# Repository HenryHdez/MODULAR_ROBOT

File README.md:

# **MODULAR ROBOT **
# **PROJECT "PCB"**
Here are all the PCB's for manufacturing the EMERGE modular robot.
# **PROJECT "Optimization_Algorithms.rar" CONTENT**
The content of this project is divided into three sections:
* The first "Module" project must be programmed in all modules of the robotic platform.
* The Second Project "Xbee_Snifer_Teraterm" must be programmed in the accessory card that has an Xbee module only (previously configured) and to perform the data registration you can use the project "Capture_Interface.rar" which is designed in MATLAB and simply begins its registration by pressing the Start button and turn on the robot.
To configure the Xbee module you can follow the following link;
http://xbee.cl/xbee-serie-2-configuracion/
* Finally, there are optimization algorithms, of which you must choose one and program it in the accessory that has the ultrasound sensor only.
# **PROJECT "Robot_Test.rar" CONTENT**
This project is used to test the different peripherals of the robot.
## Test_LED	
This code activates (Frecuency=10Hz) LED lights on each side.
## Test_All_Sensor	
The initialization routine is in charge of turning on the LED located next to each sensor, it will do it 5 times if there is communication with it, otherwise it will only do it once.
Once initialize each sensor, if one of them is obstructed turn on the LED that is next to it.
## Test_Motor	
This program turns on the motor led once it communicates with it, moves it from right to left and vice versa at intervals of 5 seconds.
## Test_Sensor_F1	
All LEDs turn on and off, if there is communication with the face sensor 1.
## Test_Sensor_F2	
All LEDs turn on and off, if there is communication with the face sensor 2.
## Test_Sensor_F3	
All LEDs turn on and off, if there is communication with the face sensor 3.
## Test_Sensor_F4	
All LEDs turn on and off, if there is communication with the face sensor 4.
## Test_CAN_Module_1
Each module sends and receives a data, if the data is accepted, turn on the led of face 2 in each module, otherwise it will not turn on.
## Test_CAN_Module_2	
CAN_Psoc_kit	
Show the information on the CAN bus on an LCD display.

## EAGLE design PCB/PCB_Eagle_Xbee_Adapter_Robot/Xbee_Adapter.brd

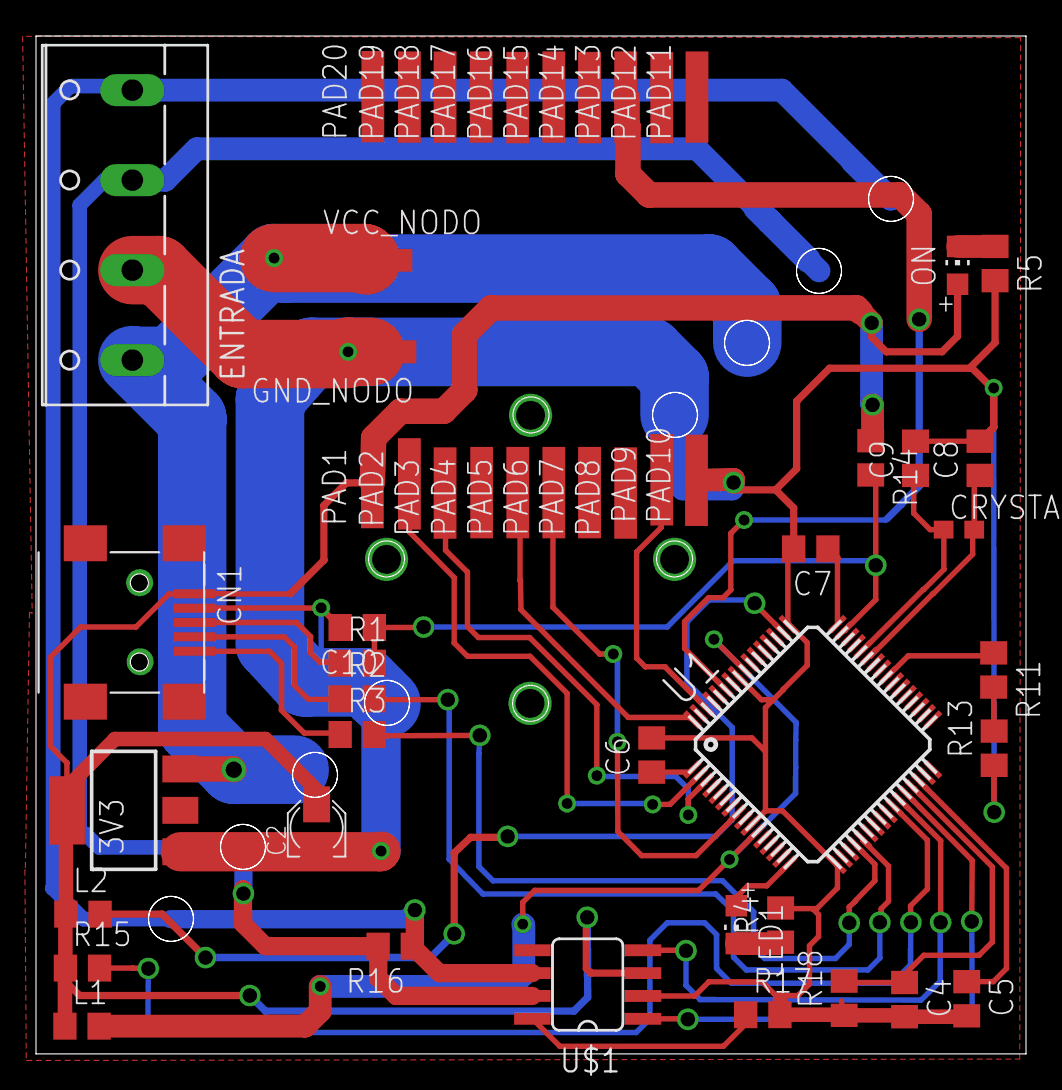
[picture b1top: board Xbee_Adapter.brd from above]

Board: 2 copper layers, 55.0 x 56.5 mm, 60 parts (0 on the bottom side), 34 nets.

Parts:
3V3: LD117AS33TR; SOT223
C2: PANASONIC_A
C4: 2200pF; C0805
C5: 10nF; C0805
C6, C7: 1u; C0805
C8: 36pF; C0805
C9: 18pF; C0805
C10: 0.1u; C0805
CANH_1_C1, CANH_1_C2: TPB2,54; B2,54
CANL_1_C1, CANL_1_C2: TPB2,54; B2,54
CN1: USB-MINIB
CRYSTAL: 32.768kHz; C0603
ENTRADA: W237-4
GND_1_C1, GND_1_C2: TPB2,54; B2,54
GND_NODO: SMD2,54-5,08
L1, L2: 330-600Ohm@1Mhz; R0805
LED1: CHIP-LED0805
ON: CHIP-LED0805
PAD1, PAD2, PAD3, PAD4, PAD5, PAD6, PAD7, PAD8, PAD9, PAD10, PAD11, PAD12, PAD13, PAD14, PAD15, PAD16, PAD17, PAD18, PAD19, PAD20: SMD2,54-5,08
R1, R2, R3, R11, R13, R15, R18: 0; R0805
R4: R0805
R5: 1K; R0805
R14: 4.7k; R0805
R16: 120; R0805
R17: 10k; R0805
U1: CY8C4247AZI-M485; TQFP64-10X10
U$1: SN65HVD230/1; SO8
VCC_2_C1, VCC_2_C2: TPB2,54; B2,54
VCC_NODO: SMD2,54-5,08

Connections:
3V3: 3V3.4, C2.+, CN1.VBUS, L1.1, L2.1, ON.A, PAD1.1, R14.1, R15.1, U$1.3
CANH: CANH_1_C1.TP, CANH_1_C2.TP, ENTRADA.3, R16.2, U$1.7
CANL: CANL_1_C1.TP, CANL_1_C2.TP, ENTRADA.4, R16.1, U$1.6
CAN_RX: U1.27, U$1.4
CAN_TX: U1.28, U$1.1
CMOD: C4.1, R18.2, U1.29
CTANK: C5.1, U1.30
GND: 3V3.1, C2.-, C4.2, C5.2, C6.2, C7.2, C8.2, C9.2, C10.2, CN1.D-, ENTRADA.2, GND_1_C1.TP, GND_1_C2.TP, GND_NODO.1, PAD10.1, R4.2, R5.2, R13.1, R17.2, R18.1, U1.10, U1.17, U1.49, U1.57, U$1.2
unnamed: CN1.D+, R1.1
unnamed: CN1.ID, R2.1
unnamed: CN1.GND, R3.1
unnamed: R11.2, R13.2
unnamed: LED1.A, U1.16
unnamed: LED1.C, R4.1
unnamed: R17.1, U$1.8
unnamed: ON.C, R5.1
P0_1: R11.1, U1.40
P0_4: C8.1, CRYSTAL.2, U1.43
P0_5: C9.1, CRYSTAL.1, U1.44
RESET_XBEE: PAD5.1, U1.64
RX_STRENGTH: PAD6.1, U1.8
SAR_BY: C6.1, U1.1
SLEEP_CTRL: PAD9.1, U1.62
SLEEP_XBEE: PAD13.1, U1.59
SWDCLK: R2.2, U1.21
SWDIO: R3.2, U1.20
UART_RX: PAD3.1, U1.3
UART_TX: PAD2.1, U1.2
VCCD: C7.1, U1.48
VCC_9-12V: 3V3.3, ENTRADA.1, VCC_2_C1.TP, VCC_2_C2.TP, VCC_NODO.1
VDDA: L1.2, U1.11, U1.56
VDDD: L2.2, U1.50
VDDIO: R15.2, U1.26
XRES: C10.1, R1.2, R14.2, U1.47

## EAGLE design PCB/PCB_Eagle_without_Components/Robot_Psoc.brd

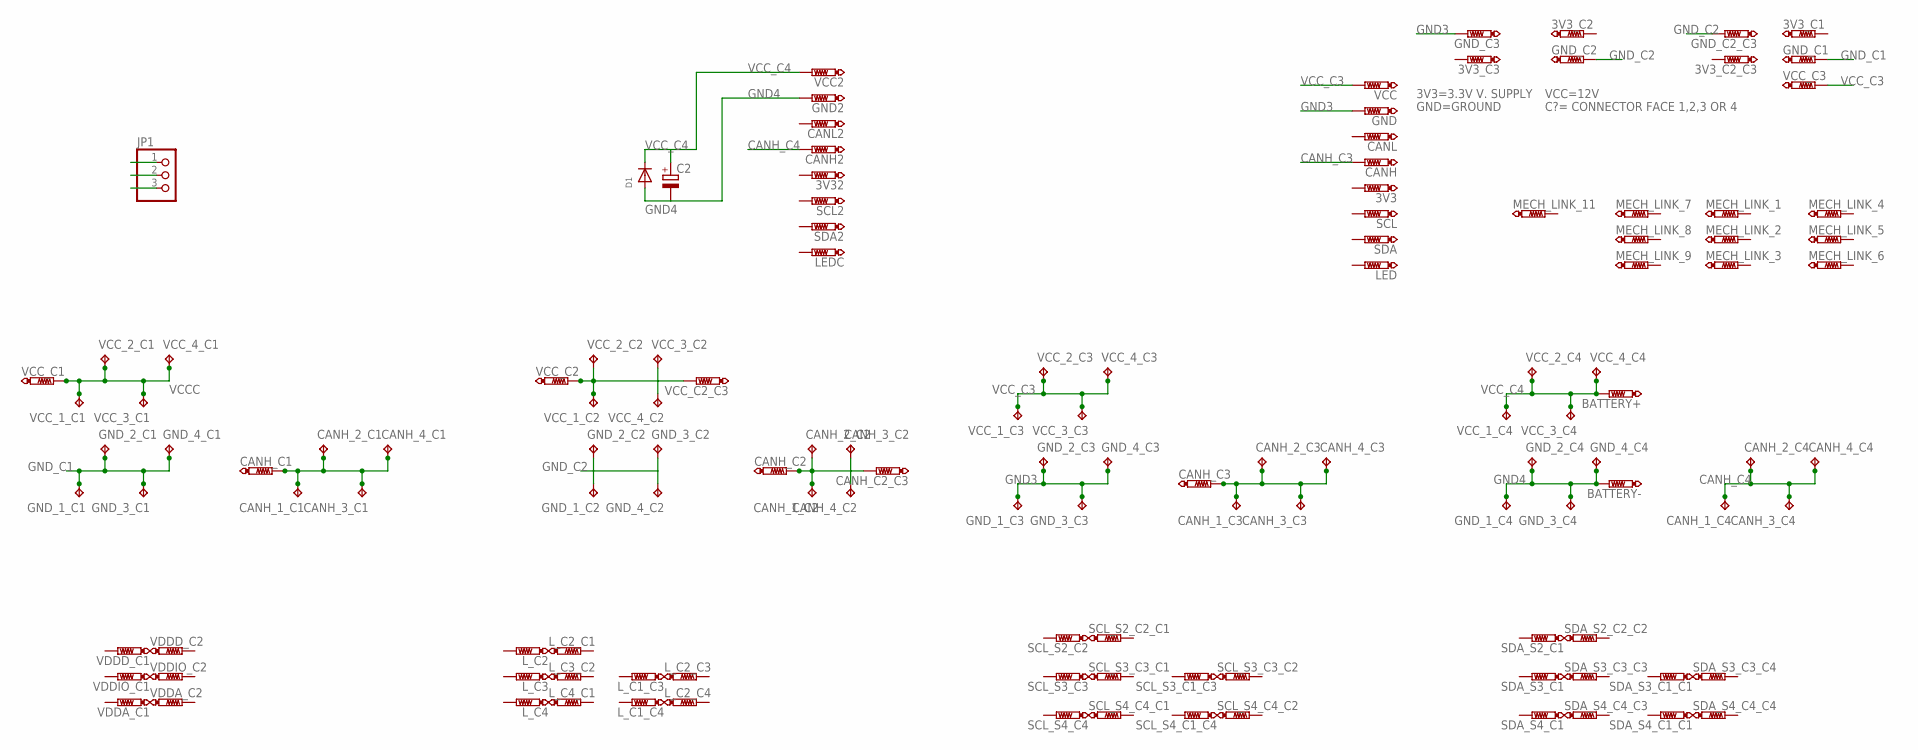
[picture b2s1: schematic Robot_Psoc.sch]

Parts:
3V3, 3V3_C1, 3V3_C2, 3V3_C2_C3, 3V3_C3, 3V32: PTR1TP11R; TP11R
BATTERY+: PTR1TP11R; TP11R
BATTERY-: PTR1TP11R; TP11R
C2: CPOL-EUUD-8X10; UD-8X10_NICHICON
CANH, CANH2: PTR1TP11R; TP11R
CANH_1_C1, CANH_1_C2, CANH_1_C3, CANH_1_C4, CANH_2_C1, CANH_2_C2, CANH_2_C3, CANH_2_C4, CANH_3_C1, CANH_3_C2, CANH_3_C3, CANH_3_C4, CANH_4_C1, CANH_4_C2, CANH_4_C3, CANH_4_C4: TPB2,54; B2,54
CANH_C1, CANH_C2, CANH_C2_C3, CANH_C3: PTR1TP11R; TP11R
CANL, CANL2: PTR1TP11R; TP11R
D1: DIODESMA; SMADIODE
GND, GND2: PTR1TP11R; TP11R
GND_1_C1, GND_1_C2, GND_1_C3, GND_1_C4, GND_2_C1, GND_2_C2, GND_2_C3, GND_2_C4, GND_3_C1, GND_3_C2, GND_3_C3, GND_3_C4, GND_4_C1, GND_4_C2, GND_4_C3, GND_4_C4: TPB2,54; B2,54
GND_C1, GND_C2, GND_C2_C3, GND_C3: PTR1TP11R; TP11R
JP1: PINHD-1X3; 1X03
LED: PTR1TP11R; TP11R
LEDC: PTR1TP11R; TP11R
L_C1_C3, L_C1_C4, L_C2, L_C2_C1, L_C2_C3, L_C2_C4, L_C3, L_C3_C2, L_C4, L_C4_C1: PTR1TP11R; TP11R
MECH_LINK_1, MECH_LINK_2, MECH_LINK_3, MECH_LINK_4, MECH_LINK_5, MECH_LINK_6, MECH_LINK_7, MECH_LINK_8, MECH_LINK_9, MECH_LINK_11: PTR1TP11R; TP11R
SCL, SCL2: PTR1TP11R; TP11R
SCL_S2_C2, SCL_S2_C2_C1, SCL_S3_C1_C3, SCL_S3_C3, SCL_S3_C3_C1, SCL_S3_C3_C2, SCL_S4_C1_C4, SCL_S4_C4, SCL_S4_C4_C1, SCL_S4_C4_C2: PTR1TP11R; TP11R
SDA, SDA2: PTR1TP11R; TP11R
SDA_S2_C1, SDA_S2_C2_C2, SDA_S3_C1, SDA_S3_C1_C1, SDA_S3_C3_C3, SDA_S3_C3_C4, SDA_S4_C1, SDA_S4_C1_C1, SDA_S4_C4_C3, SDA_S4_C4_C4: PTR1TP11R; TP11R
VCC, VCC2: PTR1TP11R; TP11R
VCC_1_C1, VCC_1_C2, VCC_1_C3, VCC_1_C4, VCC_2_C1, VCC_2_C2, VCC_2_C3, VCC_2_C4, VCC_3_C1, VCC_3_C2, VCC_3_C3, VCC_3_C4, VCC_4_C1, VCC_4_C2, VCC_4_C3, VCC_4_C4: TPB2,54; B2,54
VCC_C1, VCC_C2, VCC_C2_C3, VCC_C3: PTR1TP11R; TP11R
VDDA_C1, VDDA_C2: PTR1TP11R; TP11R
VDDD_C1, VDDD_C2: PTR1TP11R; TP11R
VDDIO_C1, VDDIO_C2: PTR1TP11R; TP11R

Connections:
CANH: CANH_1_C1.TP, CANH_2_C1.TP, CANH_3_C1.TP, CANH_4_C1.TP, CANH_C1.TP, JP1.3
CANH_C3: CANH.TP, CANH_1_C3.TP, CANH_2_C3.TP, CANH_3_C3.TP, CANH_4_C3.TP, CANH_C3.TP
CANH_C4: CANH2.TP, CANH_1_C4.TP, CANH_2_C4.TP, CANH_3_C4.TP, CANH_4_C4.TP
GND3: GND.TP, GND_1_C3.TP, GND_2_C3.TP, GND_3_C3.TP, GND_4_C3.TP, GND_C3.TP
GND4: BATTERY-.TP, C2.-, D1.A, GND2.TP, GND_1_C4.TP, GND_2_C4.TP, GND_3_C4.TP, GND_4_C4.TP
GND_C1: GND_1_C1.TP, GND_2_C1.TP, GND_3_C1.TP, GND_4_C1.TP, GND_C1.TP, JP1.2
GND_C2: GND_1_C2.TP, GND_2_C2.TP, GND_3_C2.TP, GND_4_C2.TP, GND_C2.TP, GND_C2_C3.TP
unnamed: CANH_1_C2.TP, CANH_2_C2.TP, CANH_3_C2.TP, CANH_4_C2.TP, CANH_C2.TP, CANH_C2_C3.TP
VCCC: JP1.1, VCC_1_C1.TP, VCC_2_C1.TP, VCC_3_C1.TP, VCC_4_C1.TP, VCC_C1.TP
VCC_C2: VCC_1_C2.TP, VCC_2_C2.TP, VCC_3_C2.TP, VCC_4_C2.TP, VCC_C2.TP, VCC_C2_C3.TP
VCC_C3: VCC.TP, VCC_1_C3.TP, VCC_2_C3.TP, VCC_3_C3.TP, VCC_4_C3.TP, VCC_C3.TP
VCC_C4: BATTERY+.TP, C2.+, D1.C, VCC2.TP, VCC_1_C4.TP, VCC_2_C4.TP, VCC_3_C4.TP, VCC_4_C4.TP

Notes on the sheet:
3V3=3.3V V. SUPPLY
GND=GROUND
VCC=12V
C?= CONNECTOR FACE 1,2,3 OR 4

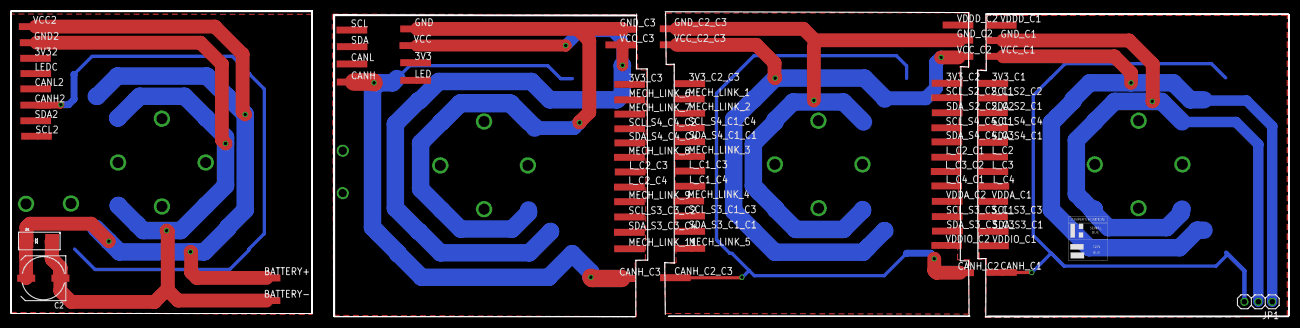
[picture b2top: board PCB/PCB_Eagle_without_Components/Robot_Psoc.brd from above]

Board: 2 copper layers, 233.5 x 55.9 mm, 131 parts (0 on the bottom side), 12 nets.

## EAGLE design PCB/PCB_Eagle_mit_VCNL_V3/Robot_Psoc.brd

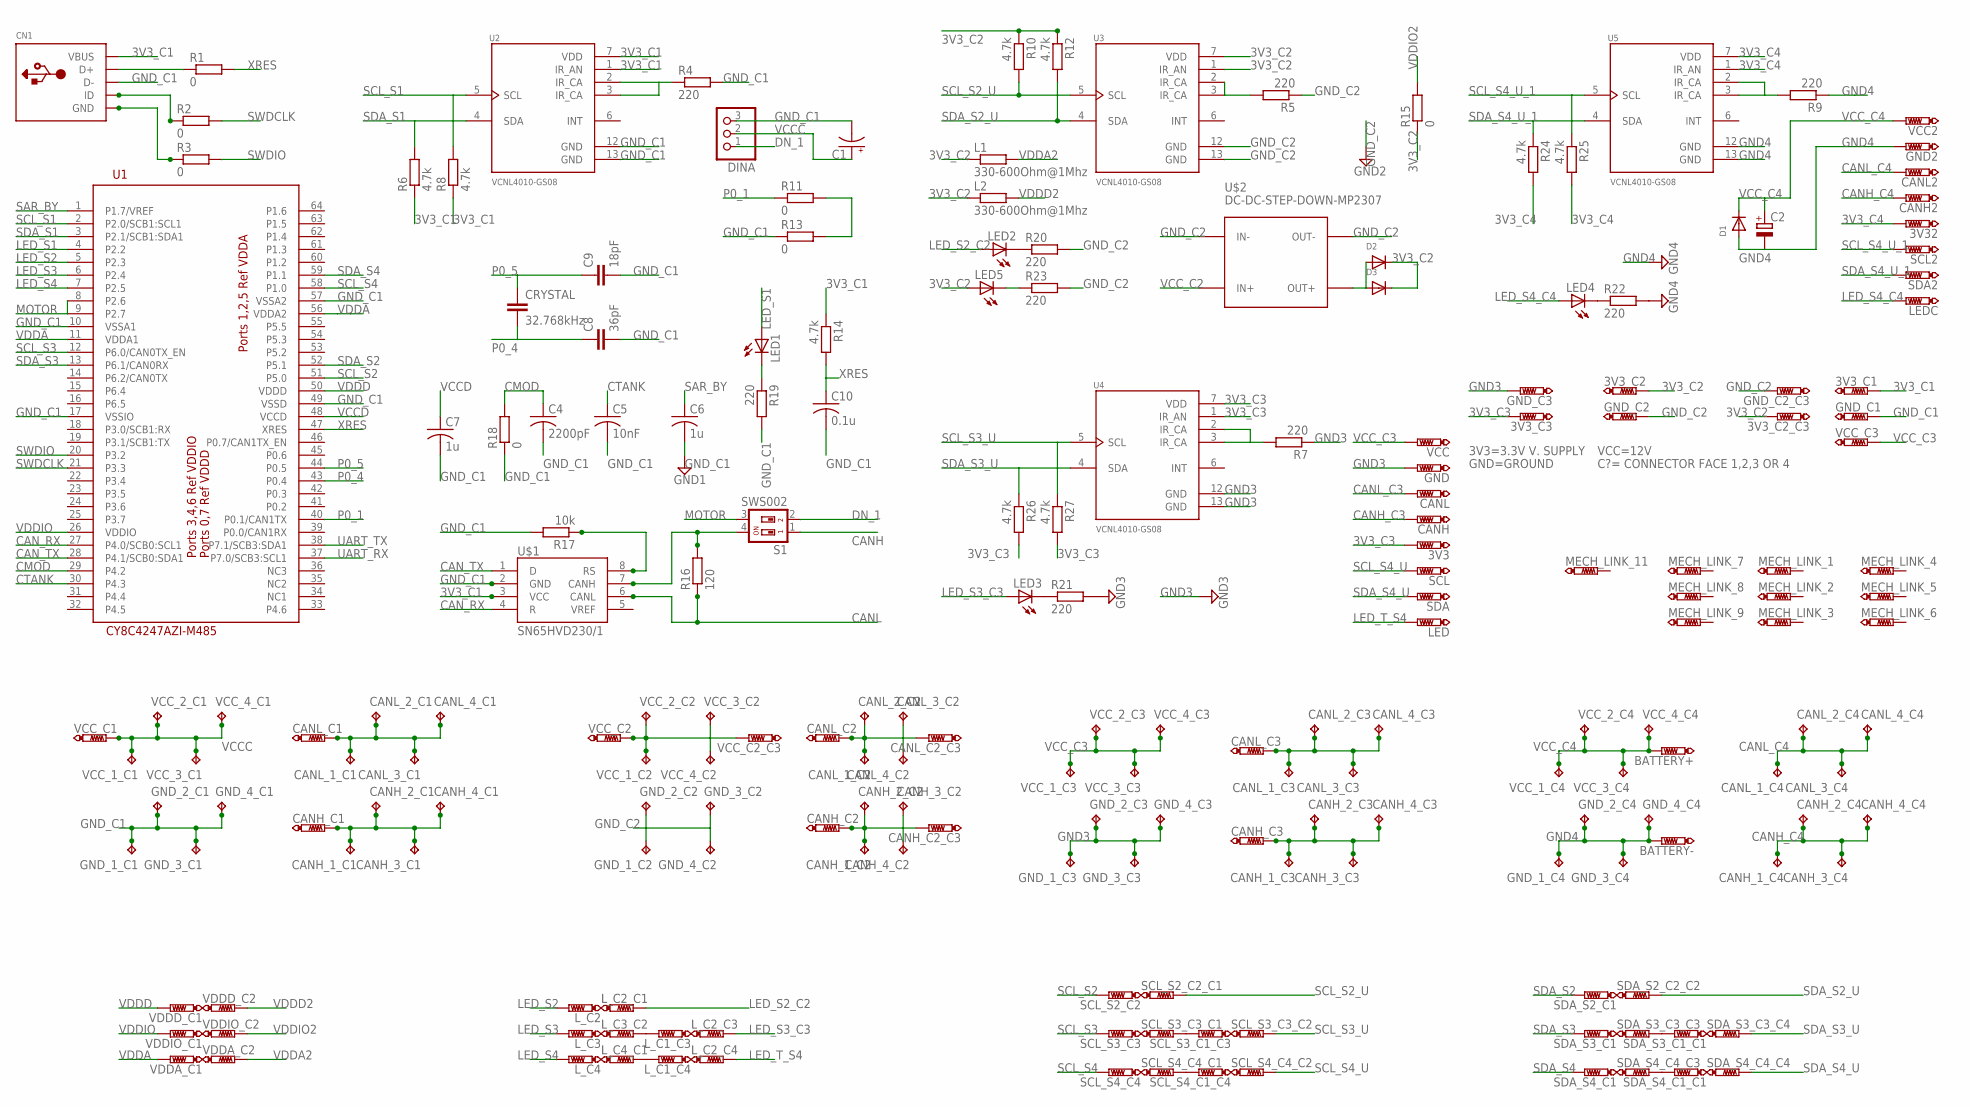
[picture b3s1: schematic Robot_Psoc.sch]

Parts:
3V3, 3V3_C1, 3V3_C2, 3V3_C2_C3, 3V3_C3, 3V32: PTR1TP11R; TP11R
BATTERY+: PTR1TP11R; TP11R
BATTERY-: PTR1TP11R; TP11R
C1: CPOL-USUD-5X5,8; UD-5X5,8_NICHICON
C2: CPOL-EUUD-8X10; UD-8X10_NICHICON
C4: 2200pF; C0805
C5: 10nF; C0805
C6, C7: 1u; C0805
C8: 36pF; C0805
C9: 18pF; C0805
C10: 0.1u; C0805
CANH, CANH2: PTR1TP11R; TP11R
CANH_1_C1, CANH_1_C2, CANH_1_C3, CANH_1_C4, CANH_2_C1, CANH_2_C2, CANH_2_C3, CANH_2_C4, CANH_3_C1, CANH_3_C2, CANH_3_C3, CANH_3_C4, CANH_4_C1, CANH_4_C2, CANH_4_C3, CANH_4_C4: TPB2,54; B2,54
CANH_C1, CANH_C2, CANH_C2_C3, CANH_C3: PTR1TP11R; TP11R
CANL, CANL2: PTR1TP11R; TP11R
CANL_1_C1, CANL_1_C2, CANL_1_C3, CANL_1_C4, CANL_2_C1, CANL_2_C2, CANL_2_C3, CANL_2_C4, CANL_3_C1, CANL_3_C2, CANL_3_C3, CANL_3_C4, CANL_4_C1, CANL_4_C2, CANL_4_C3, CANL_4_C4: TPB2,54; B2,54
CANL_C1, CANL_C2, CANL_C2_C3, CANL_C3: PTR1TP11R; TP11R
CN1: USBMINIB; USB-MINIB
CRYSTAL: 32.768kHz; C0603
D1: DIODESMA; SMADIODE
D2, D3: DIODESOD-123; SOD-123
DINA: PINHD-1X3; 1X03
GND, GND2: PTR1TP11R; TP11R
GND_1_C1, GND_1_C2, GND_1_C3, GND_1_C4, GND_2_C1, GND_2_C2, GND_2_C3, GND_2_C4, GND_3_C1, GND_3_C2, GND_3_C3, GND_3_C4, GND_4_C1, GND_4_C2, GND_4_C3, GND_4_C4: TPB2,54; B2,54
GND_C1, GND_C2, GND_C2_C3, GND_C3: PTR1TP11R; TP11R
L1, L2: 330-600Ohm@1Mhz; R0805
LED: PTR1TP11R; TP11R
LED1, LED2, LED3, LED4, LED5: LEDCHIPLED_0805; CHIPLED_0805
LEDC: PTR1TP11R; TP11R
L_C1_C3, L_C1_C4, L_C2, L_C2_C1, L_C2_C3, L_C2_C4, L_C3, L_C3_C2, L_C4, L_C4_C1: PTR1TP11R; TP11R
MECH_LINK_1, MECH_LINK_2, MECH_LINK_3, MECH_LINK_4, MECH_LINK_5, MECH_LINK_6, MECH_LINK_7, MECH_LINK_8, MECH_LINK_9, MECH_LINK_11: PTR1TP11R; TP11R
R1, R2, R3, R11, R13, R15, R18: 0; R0805
R4, R5, R7, R9, R19, R20, R21, R22, R23: 220; R0805
R6, R8, R10, R12, R14, R24, R25, R26, R27: 4.7k; R0805
R16: 120; R0805
R17: 10k; R0805
S1: SWS002; SMS-002
SCL, SCL2: PTR1TP11R; TP11R
SCL_S2_C2, SCL_S2_C2_C1, SCL_S3_C1_C3, SCL_S3_C3, SCL_S3_C3_C1, SCL_S3_C3_C2, SCL_S4_C1_C4, SCL_S4_C4, SCL_S4_C4_C1, SCL_S4_C4_C2: PTR1TP11R; TP11R
SDA, SDA2: PTR1TP11R; TP11R
SDA_S2_C1, SDA_S2_C2_C2, SDA_S3_C1, SDA_S3_C1_C1, SDA_S3_C3_C3, SDA_S3_C3_C4, SDA_S4_C1, SDA_S4_C1_C1, SDA_S4_C4_C3, SDA_S4_C4_C4: PTR1TP11R; TP11R
U1: CY8C4247AZI-M485; TQFP64-10X10
U2, U3, U4, U5: VCNL4010-GS08; XDCR_VCNL4010-GS08
U$1: SN65HVD230/1; SO8
U$2: DC-DC-STEP-DOWN-MP2307
VCC, VCC2: PTR1TP11R; TP11R
VCC_1_C1, VCC_1_C2, VCC_1_C3, VCC_1_C4, VCC_2_C1, VCC_2_C2, VCC_2_C3, VCC_2_C4, VCC_3_C1, VCC_3_C2, VCC_3_C3, VCC_3_C4, VCC_4_C1, VCC_4_C2, VCC_4_C3, VCC_4_C4: TPB2,54; B2,54
VCC_C1, VCC_C2, VCC_C2_C3, VCC_C3: PTR1TP11R; TP11R
VDDA_C1, VDDA_C2: PTR1TP11R; TP11R
VDDD_C1, VDDD_C2: PTR1TP11R; TP11R
VDDIO_C1, VDDIO_C2: PTR1TP11R; TP11R

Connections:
3V3_C1: 3V3_C1.TP, CN1.VBUS, R6.1, R8.1, R14.1, U2.1 (IR_AN), U2.7 (VDD), U$1.3 (VCC)
3V3_C2: 3V3_C2.TP, 3V3_C2_C3.TP, D2.C, D3.C, L1.1, L2.1, LED5.A, R10.1, R12.1, R15.1, U3.1 (IR_AN), U3.7 (VDD)
3V3_C3: 3V3.TP, 3V3_C3.TP, R26.2, R27.2, U4.1 (IR_AN), U4.7 (VDD)
3V3_C4: 3V32.TP, R24.2, R25.2, U5.1 (IR_AN), U5.7 (VDD)
CANH: CANH_1_C1.TP, CANH_2_C1.TP, CANH_3_C1.TP, CANH_4_C1.TP, CANH_C1.TP, S1.1
CANH_C3: CANH.TP, CANH_1_C3.TP, CANH_2_C3.TP, CANH_3_C3.TP, CANH_4_C3.TP, CANH_C3.TP
CANH_C4: CANH2.TP, CANH_1_C4.TP, CANH_2_C4.TP, CANH_3_C4.TP, CANH_4_C4.TP
CANL: CANL_1_C1.TP, CANL_2_C1.TP, CANL_3_C1.TP, CANL_4_C1.TP, CANL_C1.TP, R16.1, U$1.6 (CANL)
CANL_C3: CANL.TP, CANL_1_C3.TP, CANL_2_C3.TP, CANL_3_C3.TP, CANL_4_C3.TP, CANL_C3.TP
CANL_C4: CANL2.TP, CANL_1_C4.TP, CANL_2_C4.TP, CANL_3_C4.TP, CANL_4_C4.TP
CAN_RX: U1.27 (P4.0/SCB0:SCL1), U$1.4 (R)
CAN_TX: U1.28 (P4.1/SCB0:SDA1), U$1.1 (D)
CMOD: C4.1, R18.2, U1.29 (P4.2)
CTANK: C5.1, U1.30 (P4.3)
DN_1: DINA.1, S1.2
GND3: GND.TP, GND_1_C3.TP, GND_2_C3.TP, GND_3_C3.TP, GND_4_C3.TP, GND_C3.TP, R7.1, R21.2, U4.12 (GND), U4.13 (GND)
GND4: BATTERY-.TP, C2.-, D1.A, GND2.TP, GND_1_C4.TP, GND_2_C4.TP, GND_3_C4.TP, GND_4_C4.TP, R9.1, R22.2, U5.12 (GND), U5.13 (GND)
GND_C1: C1.-, C4.2, C5.2, C6.2, C7.2, C8.2, C9.2, C10.2, CN1.D-, DINA.3, GND_1_C1.TP, GND_2_C1.TP, GND_3_C1.TP, GND_4_C1.TP, GND_C1.TP, R4.2, R13.1, R17.2, R18.1, R19.2, U1.10 (VSSA1), U1.17 (VSSIO), U1.49 (VSSD), U1.57 (VSSA2), U2.12 (GND), U2.13 (GND), U$1.2 (GND)
GND_C2: GND_1_C2.TP, GND_2_C2.TP, GND_3_C2.TP, GND_4_C2.TP, GND_C2.TP, GND_C2_C3.TP, R5.1, R20.2, R23.2, U3.12 (GND), U3.13 (GND), U$2.IN-, U$2.OUT-
LED_S1: LED1.A, U1.4 (P2.2)
LED_S2: L_C2.TP, U1.5 (P2.3)
LED_S2_C2: LED2.A, L_C2_C1.TP
LED_S3: L_C3.TP, U1.6 (P2.4)
LED_S3_C3: LED3.A, L_C2_C3.TP
LED_S4: L_C4.TP, U1.7 (P2.5)
LED_S4_C4: LED4.A, LEDC.TP
LED_T_S4: LED.TP, L_C2_C4.TP
MOTOR: S1.3, U1.8 (P2.6), U1.9 (P2.7)
unnamed: CN1.D+, R1.1
unnamed: CN1.ID, R2.1
unnamed: CN1.GND, R3.1
unnamed: R11.2, R13.2
unnamed: R16.2, S1.4, U$1.7 (CANH)
unnamed: CANH_1_C2.TP, CANH_2_C2.TP, CANH_3_C2.TP, CANH_4_C2.TP, CANH_C2.TP, CANH_C2_C3.TP
unnamed: R7.2, U4.2 (IR_CA), U4.3 (IR_CA)
unnamed: R17.1, U$1.8 (RS)
unnamed: SDA_S3_C1_C1.TP, SDA_S3_C3_C3.TP
unnamed: LED1.C, R19.1
unnamed: LED2.C, R20.1
unnamed: LED3.C, R21.1
unnamed: LED4.C, R22.1
unnamed: LED5.C, R23.1
unnamed: L_C1_C4.TP, L_C4_C1.TP
unnamed: R4.1, U2.2 (IR_CA), U2.3 (IR_CA)
unnamed: L_C1_C3.TP, L_C3_C2.TP
unnamed: D2.A, D3.A, U$2.OUT+
unnamed: SCL_S3_C1_C3.TP, SCL_S3_C3_C1.TP
unnamed: SCL_S4_C1_C4.TP, SCL_S4_C4_C1.TP
unnamed: CANL_1_C2.TP, CANL_2_C2.TP, CANL_3_C2.TP, CANL_4_C2.TP, CANL_C2.TP, CANL_C2_C3.TP
unnamed: R5.2, U3.2 (IR_CA), U3.3 (IR_CA)
unnamed: SDA_S4_C1_C1.TP, SDA_S4_C4_C3.TP
unnamed: R9.2, U5.2 (IR_CA), U5.3 (IR_CA)
P0_1: R11.1, U1.40 (P0.1/CAN1TX)
P0_4: C8.1, CRYSTAL.2, U1.43 (P0.4)
P0_5: C9.1, CRYSTAL.1, U1.44 (P0.5)
SAR_BY: C6.1, U1.1 (P1.7/VREF)
SCL_S1: R8.2, U1.2 (P2.0/SCB1:SCL1), U2.5 (SCL)
SCL_S2: SCL_S2_C2.TP, U1.51 (P5.0)
SCL_S2_U: R10.2, SCL_S2_C2_C1.TP, U3.5 (SCL)
SCL_S3: SCL_S3_C3.TP, U1.12 (P6.0/CAN0TX_EN)
SCL_S3_U: R27.1, SCL_S3_C3_C2.TP, U4.5 (SCL)
SCL_S4: SCL_S4_C4.TP, U1.58 (P1.0)
SCL_S4_U: SCL.TP, SCL_S4_C4_C2.TP
SCL_S4_U_1: R25.1, SCL2.TP, U5.5 (SCL)
SDA_S1: R6.2, U1.3 (P2.1/SCB1:SDA1), U2.4 (SDA)
SDA_S2: SDA_S2_C1.TP, U1.52 (P5.1)
SDA_S2_U: R12.2, SDA_S2_C2_C2.TP, U3.4 (SDA)
SDA_S3: SDA_S3_C1.TP, U1.13 (P6.1/CAN0RX)
SDA_S3_U: R26.1, SDA_S3_C3_C4.TP, U4.4 (SDA)
SDA_S4: SDA_S4_C1.TP, U1.59 (P1.1)
SDA_S4_U: SDA.TP, SDA_S4_C4_C4.TP
SDA_S4_U_1: R24.1, SDA2.TP, U5.4 (SDA)
SWDCLK: R2.2, U1.21 (P3.3)
SWDIO: R3.2, U1.20 (P3.2)
UART_RX: U1.37 (P7.0/SCB3:SCL1)
UART_TX: U1.38 (P7.1/SCB3:SDA1)
VCCC: C1.+, DINA.2, VCC_1_C1.TP, VCC_2_C1.TP, VCC_3_C1.TP, VCC_4_C1.TP, VCC_C1.TP
VCCD: C7.1, U1.48 (VCCD)
VCC_C2: U$2.IN+, VCC_1_C2.TP, VCC_2_C2.TP, VCC_3_C2.TP, VCC_4_C2.TP, VCC_C2.TP, VCC_C2_C3.TP
VCC_C3: VCC.TP, VCC_1_C3.TP, VCC_2_C3.TP, VCC_3_C3.TP, VCC_4_C3.TP, VCC_C3.TP
VCC_C4: BATTERY+.TP, C2.+, D1.C, VCC2.TP, VCC_1_C4.TP, VCC_2_C4.TP, VCC_3_C4.TP, VCC_4_C4.TP
VDDA: U1.11 (VDDA1), U1.56 (VDDA2), VDDA_C1.TP
VDDA2: L1.2, VDDA_C2.TP
VDDD: U1.50 (VDDD), VDDD_C1.TP
VDDD2: L2.2, VDDD_C2.TP
VDDIO: U1.26 (VDDIO), VDDIO_C1.TP
VDDIO2: R15.2, VDDIO_C2.TP
XRES: C10.1, R1.2, R14.2, U1.47 (XRES)

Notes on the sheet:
3V3=3.3V V. SUPPLY
GND=GROUND
VCC=12V
C?= CONNECTOR FACE 1,2,3 OR 4

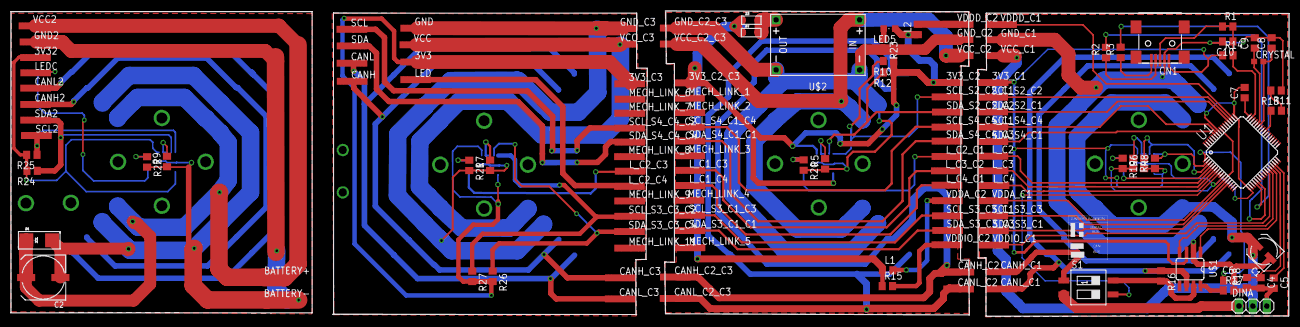
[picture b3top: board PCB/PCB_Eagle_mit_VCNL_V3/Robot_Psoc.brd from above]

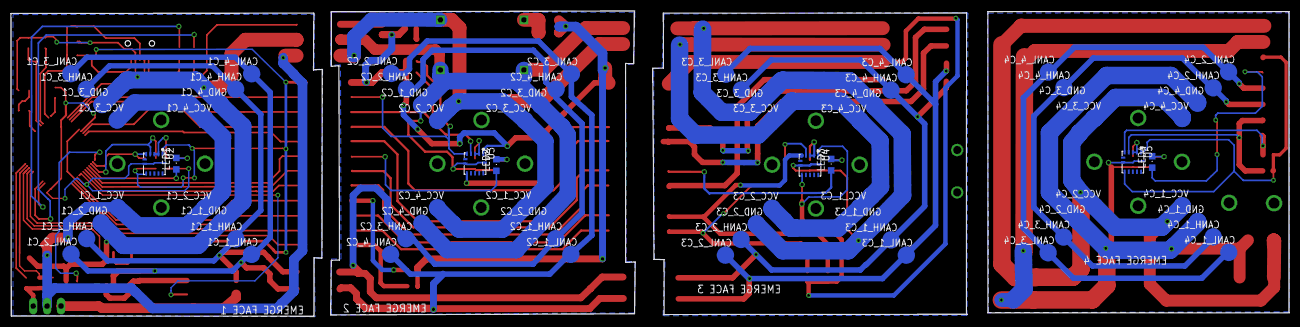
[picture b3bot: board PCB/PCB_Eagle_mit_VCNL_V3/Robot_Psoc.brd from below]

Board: 2 copper layers, 233.4 x 55.7 mm, 205 parts (8 on the bottom side), 86 nets.

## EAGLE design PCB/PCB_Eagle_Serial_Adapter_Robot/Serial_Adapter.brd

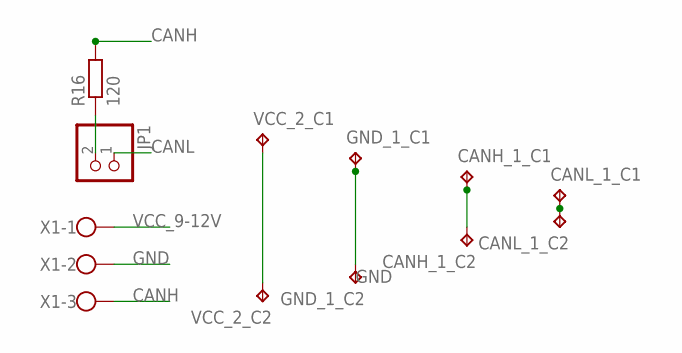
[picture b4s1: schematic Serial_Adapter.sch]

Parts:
CANH_1_C1, CANH_1_C2: TPB2,54; B2,54
CANL_1_C1, CANL_1_C2: TPB2,54; B2,54
GND_1_C1, GND_1_C2: TPB2,54; B2,54
JP1: PINHD-1X2; 1X02
R16: 120; R0805
VCC_2_C1, VCC_2_C2: TPB2,54; B2,54
X1: W237-103

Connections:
CANH: CANH_1_C1.TP, CANH_1_C2.TP, R16.2, X1.3
CANL: CANL_1_C1.TP, CANL_1_C2.TP, JP1.1
GND: GND_1_C1.TP, GND_1_C2.TP, X1.2
unnamed: JP1.2, R16.1
VCC_9-12V: VCC_2_C1.TP, VCC_2_C2.TP, X1.1

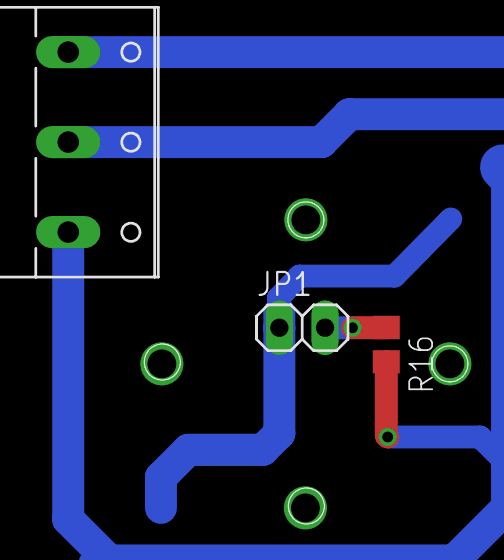
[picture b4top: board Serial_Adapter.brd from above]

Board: 2 copper layers, 11 parts (0 on the bottom side), 5 nets.

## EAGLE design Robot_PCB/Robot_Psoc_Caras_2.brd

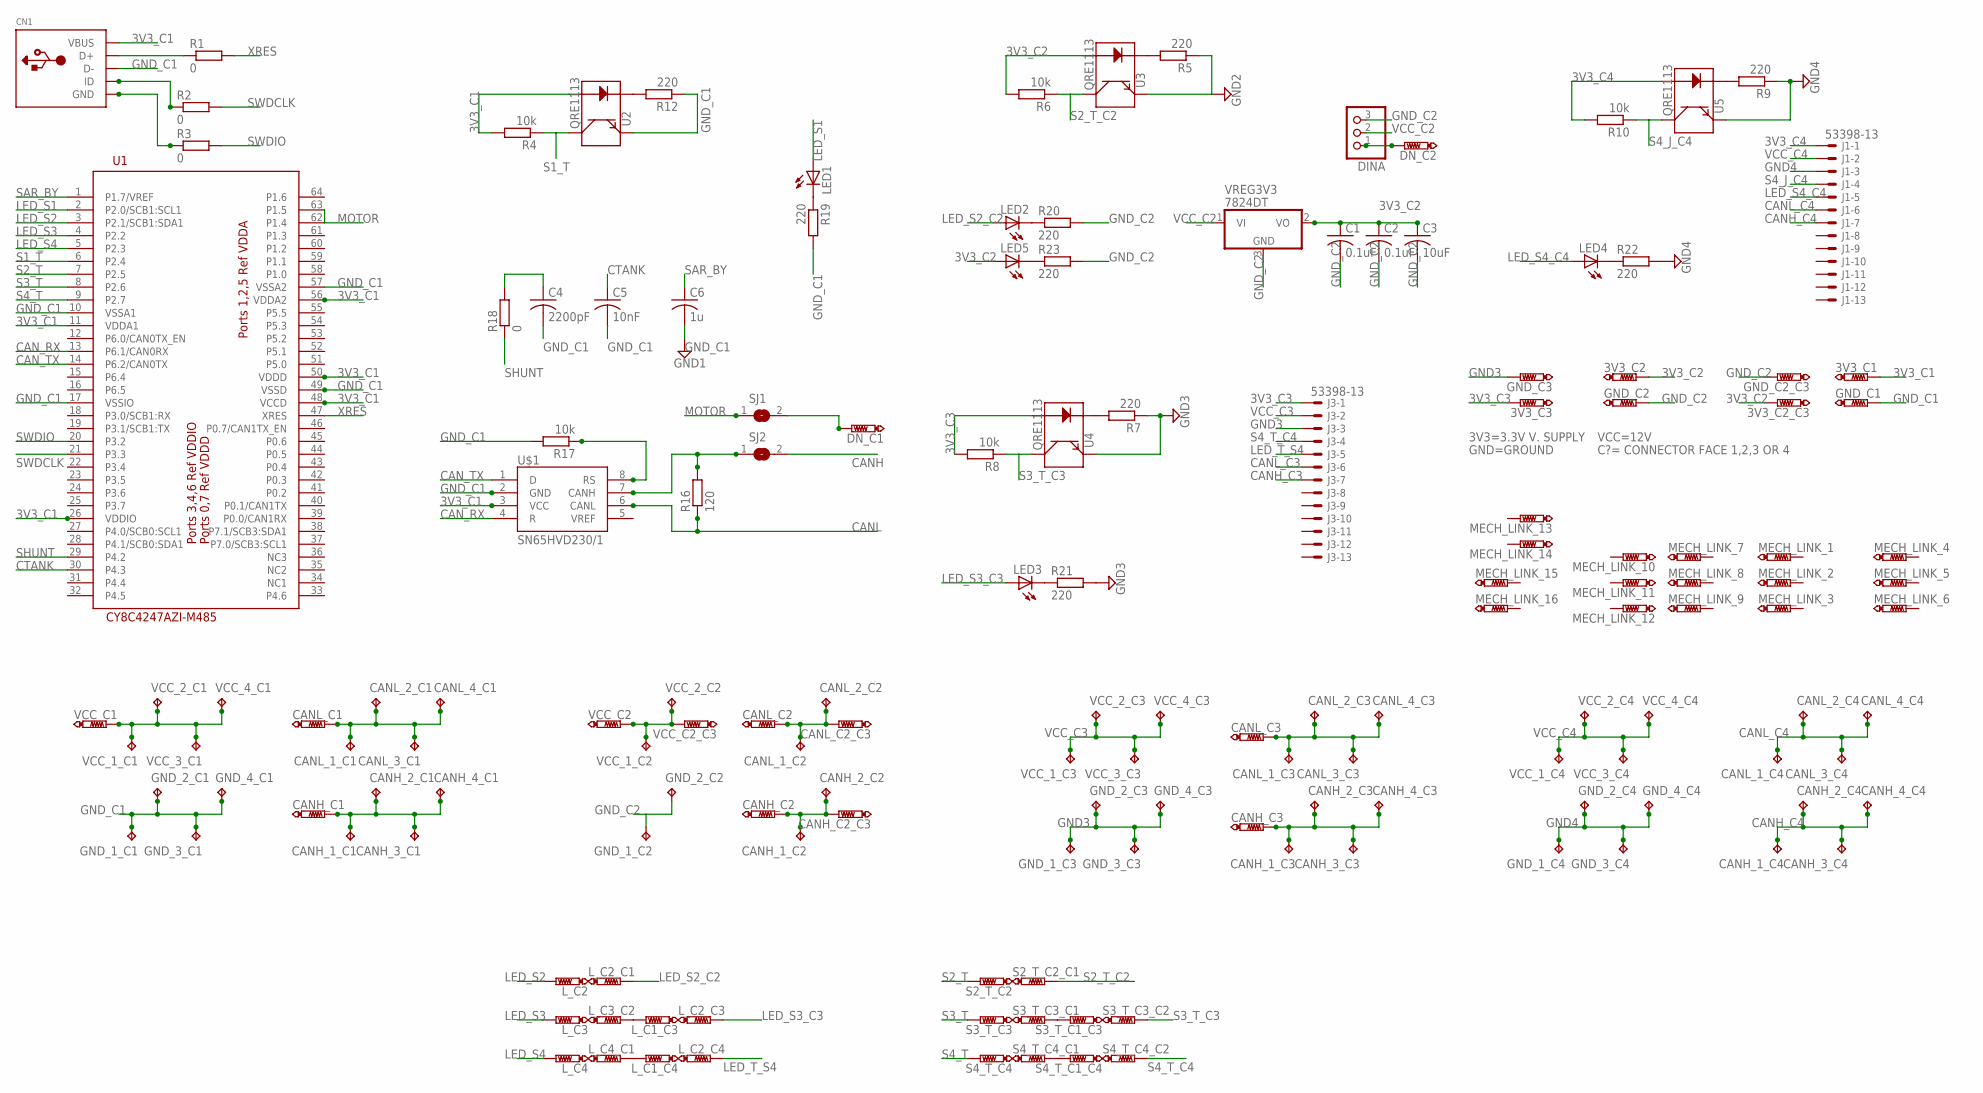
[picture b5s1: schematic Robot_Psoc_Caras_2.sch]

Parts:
3V3_C1, 3V3_C2, 3V3_C2_C3, 3V3_C3: PTR1TP11R; TP11R
C1, C2: 0.1uF; C0805
C3: 10uF; C4532
C4: 2200pF; C0805
C5: 10nF; C0805
C6: 1u; C0805
CANH_1_C1, CANH_1_C2, CANH_1_C3, CANH_1_C4, CANH_2_C1, CANH_2_C2, CANH_2_C3, CANH_2_C4, CANH_3_C1, CANH_3_C3, CANH_3_C4, CANH_4_C1, CANH_4_C3, CANH_4_C4: TPB2,54; B2,54
CANH_C1, CANH_C2, CANH_C2_C3, CANH_C3: PTR1TP11R; TP11R
CANL_1_C1, CANL_1_C2, CANL_1_C3, CANL_1_C4, CANL_2_C1, CANL_2_C2, CANL_2_C3, CANL_2_C4, CANL_3_C1, CANL_3_C3, CANL_3_C4, CANL_4_C1, CANL_4_C3, CANL_4_C4: TPB2,54; B2,54
CANL_C1, CANL_C2, CANL_C2_C3, CANL_C3: PTR1TP11R; TP11R
CN1: USBMINIB; USB-MINIB
DINA: PINHD-1X3; 1X03
DN_C1, DN_C2: PTR1TP11R; TP11R
GND_1_C1, GND_1_C2, GND_1_C3, GND_1_C4, GND_2_C1, GND_2_C2, GND_2_C3, GND_2_C4, GND_3_C1, GND_3_C3, GND_3_C4, GND_4_C1, GND_4_C3, GND_4_C4: TPB2,54; B2,54
GND_C1, GND_C2, GND_C2_C3, GND_C3: PTR1TP11R; TP11R
J1, J3: 53398-13
LED1, LED2, LED3, LED4, LED5: LEDCHIPLED_0805; CHIPLED_0805
L_C1_C3, L_C1_C4, L_C2, L_C2_C1, L_C2_C3, L_C2_C4, L_C3, L_C3_C2, L_C4, L_C4_C1: PTR1TP11R; TP11R
MECH_LINK_1, MECH_LINK_2, MECH_LINK_3, MECH_LINK_4, MECH_LINK_5, MECH_LINK_6, MECH_LINK_7, MECH_LINK_8, MECH_LINK_9, MECH_LINK_10, MECH_LINK_11, MECH_LINK_12, MECH_LINK_13, MECH_LINK_14, MECH_LINK_15, MECH_LINK_16: PTR1TP11R; TP11R
R1, R2, R3, R18: 0; R0805
R4, R6, R8, R10, R17: 10k; R0805
R5, R7, R9, R12, R19, R20, R21, R22, R23: 220; R0805
R16: 120; R0805
S2_T_C2, S2_T_C2_C1, S3_T_C1_C3, S3_T_C3, S3_T_C3_C1, S3_T_C3_C2, S4_T_C1_C4, S4_T_C4, S4_T_C4_C1, S4_T_C4_C2: PTR1TP11R; TP11R
SJ1, SJ2: SJ
U1: CY8C4247AZI-M485; TQFP64-10X10
U2, U3, U4, U5: QRE1113
U$1: SN65HVD230/1; SO8
VCC_1_C1, VCC_1_C2, VCC_1_C3, VCC_1_C4, VCC_2_C1, VCC_2_C2, VCC_2_C3, VCC_2_C4, VCC_3_C1, VCC_3_C3, VCC_3_C4, VCC_4_C1, VCC_4_C3, VCC_4_C4: TPB2,54; B2,54
VCC_C1, VCC_C2, VCC_C2_C3: PTR1TP11R; TP11R
VREG3V3: 7824DT; TO252

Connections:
3V3_C1: 3V3_C1.TP, CN1.VBUS, R4.2, U1.11 (VDDA1), U1.26 (VDDIO), U1.48 (VCCD), U1.50 (VDDD), U1.56 (VDDA2), U2.1 (A), U$1.3 (VCC)
3V3_C2: 3V3_C2.TP, 3V3_C2_C3.TP, C1.1, C2.1, C3.1, LED5.A, R6.2, U3.1 (A), VREG3V3.2 (VO)
3V3_C3: 3V3_C3.TP, J3.1, R8.2, U4.1 (A)
3V3_C4: J1.1, R10.2, U5.1 (A)
CANH: CANH_1_C1.TP, CANH_2_C1.TP, CANH_3_C1.TP, CANH_4_C1.TP, CANH_C1.TP, SJ2.2
CANH_C3: CANH_1_C3.TP, CANH_2_C3.TP, CANH_3_C3.TP, CANH_4_C3.TP, CANH_C3.TP, J3.7
CANH_C4: CANH_1_C4.TP, CANH_2_C4.TP, CANH_3_C4.TP, CANH_4_C4.TP, J1.7
CANL: CANL_1_C1.TP, CANL_2_C1.TP, CANL_3_C1.TP, CANL_4_C1.TP, CANL_C1.TP, R16.1, U$1.6 (CANL)
CANL_C3: CANL_1_C3.TP, CANL_2_C3.TP, CANL_3_C3.TP, CANL_4_C3.TP, CANL_C3.TP, J3.6
CANL_C4: CANL_1_C4.TP, CANL_2_C4.TP, CANL_3_C4.TP, CANL_4_C4.TP, J1.6
CAN_RX: U1.13 (P6.1/CAN0RX), U$1.4 (R)
CAN_TX: U1.14 (P6.2/CAN0TX), U$1.1 (D)
CTANK: C5.1, U1.30 (P4.3)
GND3: GND_1_C3.TP, GND_2_C3.TP, GND_3_C3.TP, GND_4_C3.TP, GND_C3.TP, J3.3, R7.1, R21.2, U4.4 (E)
GND4: GND_1_C4.TP, GND_2_C4.TP, GND_3_C4.TP, GND_4_C4.TP, J1.3, R9.1, R22.2, U5.4 (E)
GND_C1: C4.2, C5.2, C6.2, CN1.D-, GND_1_C1.TP, GND_2_C1.TP, GND_3_C1.TP, GND_4_C1.TP, GND_C1.TP, R12.1, R17.2, R19.2, U1.10 (VSSA1), U1.17 (VSSIO), U1.49 (VSSD), U1.57 (VSSA2), U2.4 (E), U$1.2 (GND)
GND_C2: C1.2, C2.2, C3.2, DINA.3, GND_1_C2.TP, GND_2_C2.TP, GND_C2.TP, GND_C2_C3.TP, R5.1, R20.2, R23.2, U3.4 (E), VREG3V3.3 (GND)
LED_S1: LED1.A, U1.2 (P2.0/SCB1:SCL1)
LED_S2: L_C2.TP, U1.3 (P2.1/SCB1:SDA1)
LED_S2_C2: LED2.A, L_C2_C1.TP
LED_S3: L_C3.TP, U1.4 (P2.2)
LED_S3_C3: LED3.A, L_C2_C3.TP
LED_S4: L_C4.TP, U1.5 (P2.3)
LED_S4_C4: J1.5, LED4.A
LED_T_S4: J3.5, L_C2_C4.TP
MOTOR: SJ1.1, U1.62 (P1.4), U1.63 (P1.5)
unnamed: CN1.D+, R1.1
unnamed: CN1.ID, R2.1
unnamed: CN1.GND, R3.1
unnamed: R16.2, SJ2.1, U$1.7 (CANH)
unnamed: R5.2, U3.2 (K)
unnamed: CANH_1_C2.TP, CANH_2_C2.TP, CANH_C2.TP, CANH_C2_C3.TP
unnamed: R7.2, U4.2 (K)
unnamed: R17.1, U$1.8 (RS)
unnamed: R9.2, U5.2 (K)
unnamed: C4.1, R18.2
unnamed: DN_C1.TP, SJ1.2
unnamed: LED1.C, R19.1
unnamed: LED2.C, R20.1
unnamed: LED3.C, R21.1
unnamed: LED4.C, R22.1
unnamed: LED5.C, R23.1
unnamed: DINA.1, DN_C2.TP
unnamed: L_C1_C4.TP, L_C4_C1.TP
unnamed: R12.2, U2.2 (K)
unnamed: L_C1_C3.TP, L_C3_C2.TP
unnamed: S3_T_C1_C3.TP, S3_T_C3_C1.TP
unnamed: S4_T_C1_C4.TP, S4_T_C4_C1.TP
unnamed: VCC_1_C1.TP, VCC_2_C1.TP, VCC_3_C1.TP, VCC_4_C1.TP, VCC_C1.TP
unnamed: CANL_1_C2.TP, CANL_2_C2.TP, CANL_C2.TP, CANL_C2_C3.TP
S1_T: R4.1, U1.6 (P2.4), U2.3 (C)
S2_T: S2_T_C2.TP, U1.7 (P2.5)
S2_T_C2: R6.1, S2_T_C2_C1.TP, U3.3 (C)
S3_T: S3_T_C3.TP, U1.8 (P2.6)
S3_T_C3: R8.1, S3_T_C3_C2.TP, U4.3 (C)
S4_J_C4: J1.4, R10.1, U5.3 (C)
S4_T: S4_T_C4.TP, U1.9 (P2.7)
S4_T_C4: J3.4, S4_T_C4_C2.TP
SAR_BY: C6.1, U1.1 (P1.7/VREF)
SHUNT: R18.1, U1.29 (P4.2)
SWDCLK: R2.2, U1.21 (P3.3)
SWDIO: R3.2, U1.20 (P3.2)
VCC_C2: DINA.2, VCC_1_C2.TP, VCC_2_C2.TP, VCC_C2.TP, VCC_C2_C3.TP, VREG3V3.1 (VI)
VCC_C3: J3.2, VCC_1_C3.TP, VCC_2_C3.TP, VCC_3_C3.TP, VCC_4_C3.TP
VCC_C4: J1.2, VCC_1_C4.TP, VCC_2_C4.TP, VCC_3_C4.TP, VCC_4_C4.TP
XRES: R1.2, U1.47 (XRES)

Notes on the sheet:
3V3=3.3V V. SUPPLY
GND=GROUND
VCC=12V
C?= CONNECTOR FACE 1,2,3 OR 4

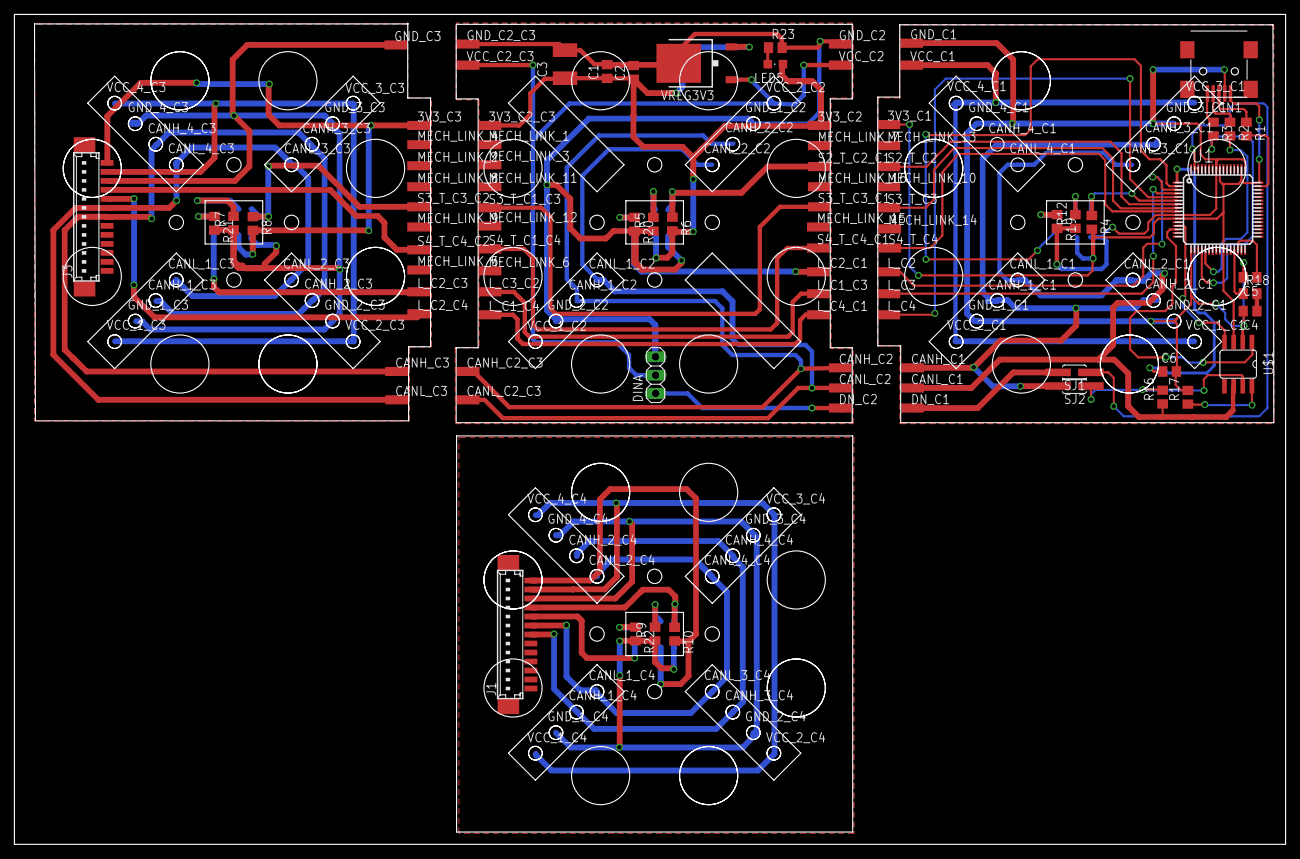
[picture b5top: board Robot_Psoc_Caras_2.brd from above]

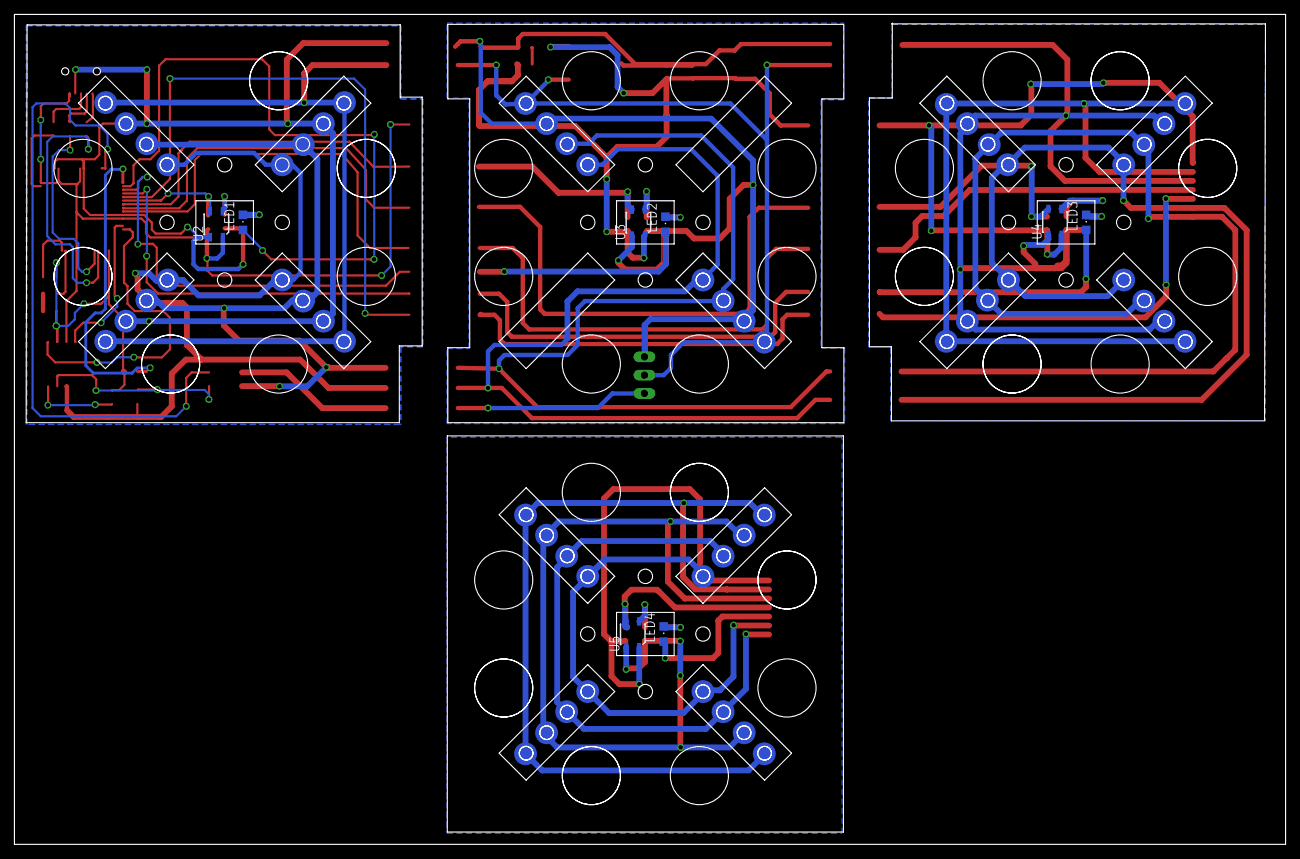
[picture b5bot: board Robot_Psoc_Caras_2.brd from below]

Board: 2 copper layers, 176.5 x 115.2 mm, 156 parts (8 on the bottom side), 66 nets.

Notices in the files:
parts and their libraries:
diy-modules: Released under the Creative Commons Attribution 4.0 International License: http://creativecommons.org/licenses/by/4.0
SparkFun-Sensors: Licensing: Creative Commons ShareAlike 4.0 International - https://creativecommons.org/licenses/by-sa/4.0
